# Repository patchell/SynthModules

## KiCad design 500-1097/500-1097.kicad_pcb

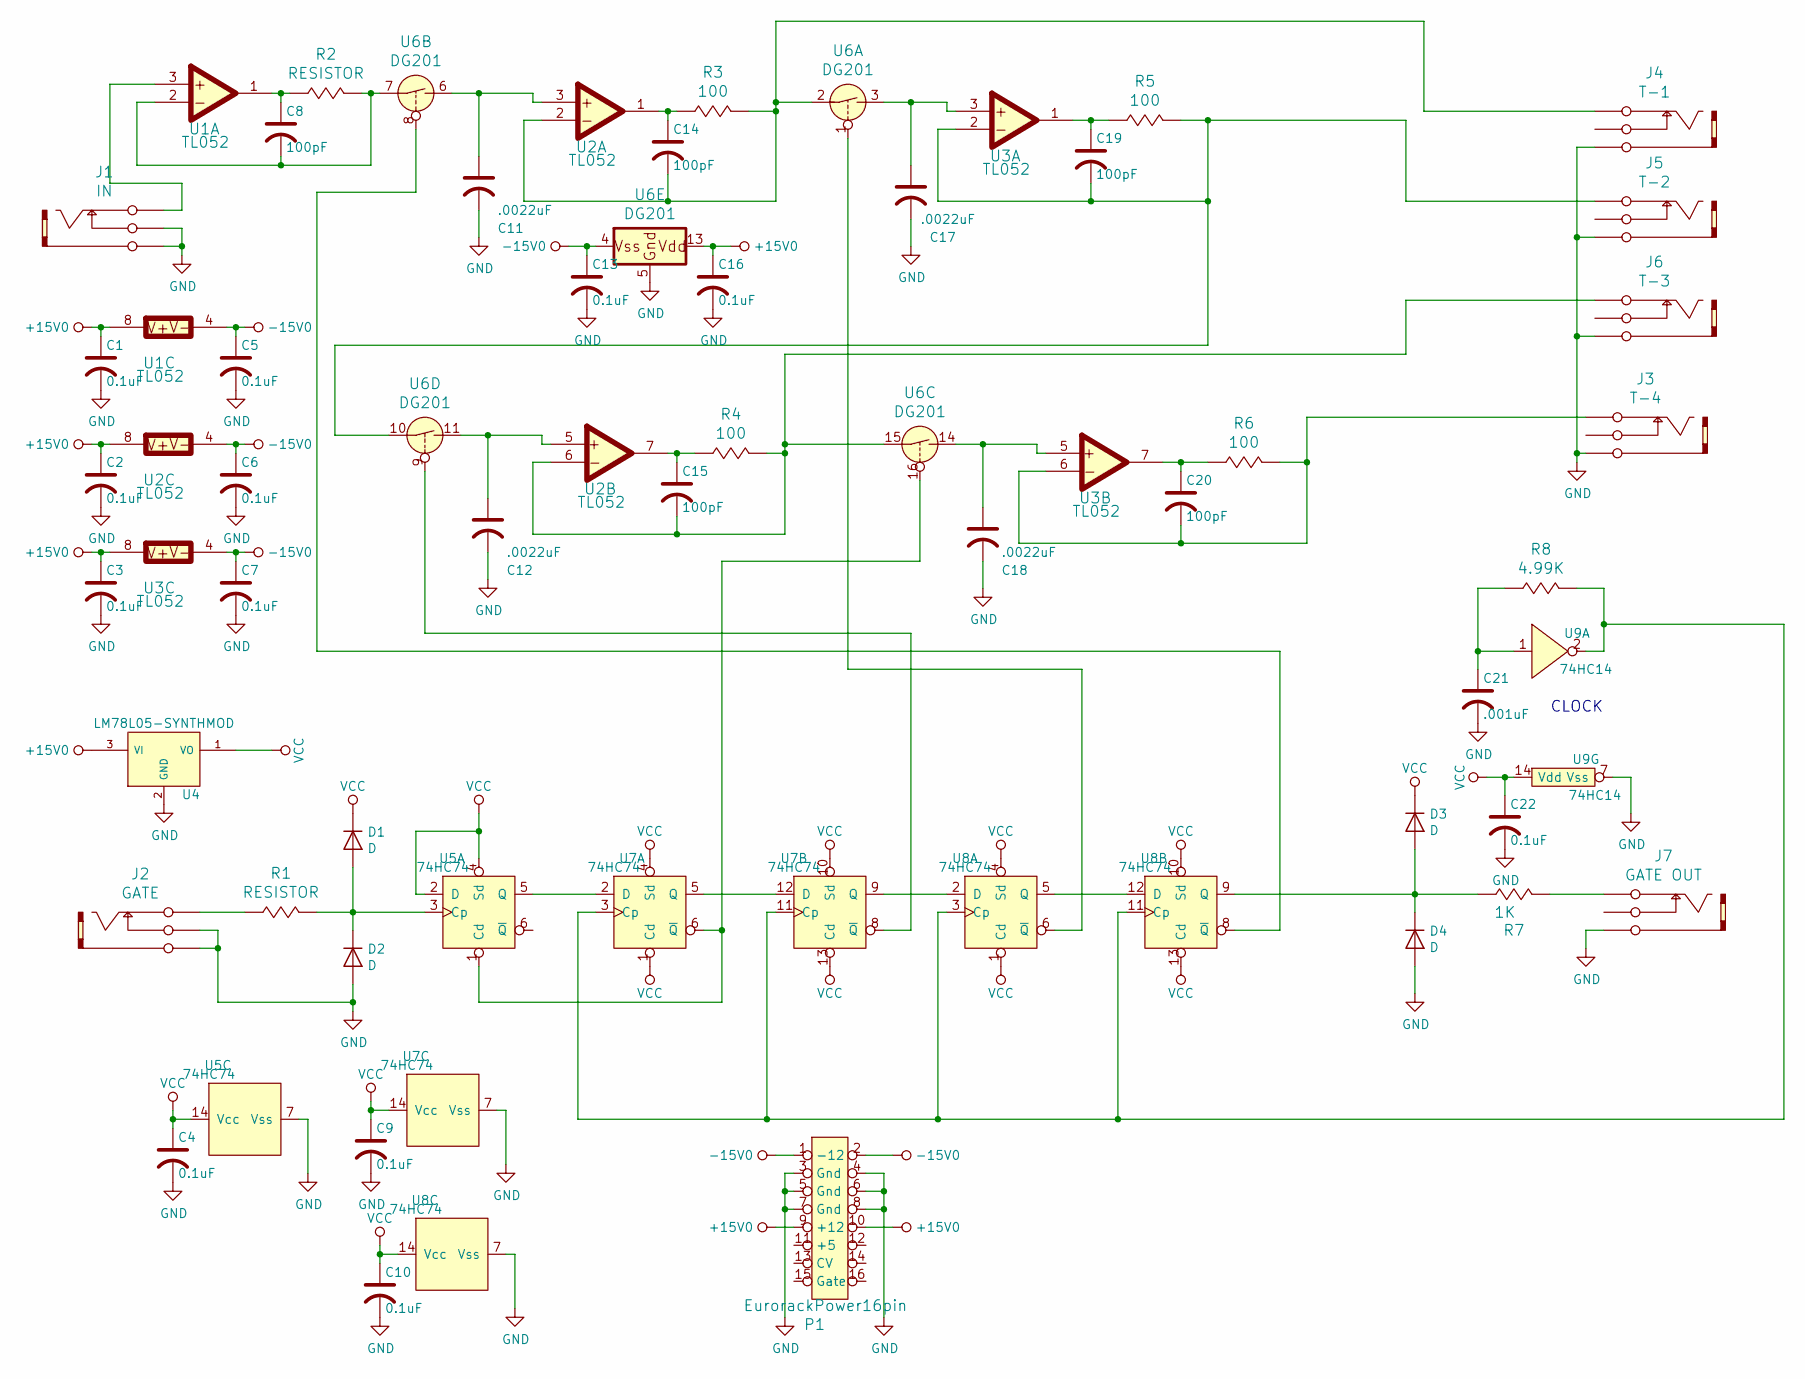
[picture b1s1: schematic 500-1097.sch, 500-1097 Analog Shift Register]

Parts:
C1, C2, C3, C4, C5, C6, C7, C9, C10, C13, C16, C22: 0.1uF; CAP-Bypass-0.3
C8, C14, C15, C19, C20: 100pF; CAP-0.1
C11, C12, C17, C18: .0022uF; CAP-AXIAL-0.5x0.2
C21: .001uF; CAP-GREENIE-0.2
D1, D2, D3, D4: D; DIODE0.4
J1: IN; PHONE-SC112A
J2: GATE; PHONE-SC112A
J3: T-4; PHONE-SC112A
J4: T-1; PHONE-SC112A
J5: T-2; PHONE-SC112A
J6: T-3; PHONE-SC112A
J7: GATE OUT; PHONE-SC112A
P1: EurorackPower16pin; IDC8x2_Vert
R1, R2: RESISTOR; AXIAL0.4
R3, R4, R5, R6: 100; AXIAL0.4
R7: 1K; AXIAL0.4
R8: 4.99K; AXIAL0.4
U1, U2, U3: TL052; DIP8.3
U4: LM78L05-SYNTHMOD; TO92
U5, U7, U8: 74HC74; DIP-14.3
U6: DG201; DIP-16.3
U9: 74HC14; DIP-14.3

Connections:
+15V0: C1.1, C2.1, C3.1, C16.1, P1.9 (+12), P1.10, U1.8 (V+), U2.8 (V+), U3.8 (V+), U4.3 (VI), U6.13 (Vdd)
-15V0: C5.1, C6.1, C7.1, C13.1, P1.1 (-12), P1.2, U1.4 (V-), U2.4 (V-), U3.4 (V-), U6.4 (Vss)
GND: C1.2, C2.2, C3.2, C4.2, C5.2, C6.2, C7.2, C9.2, C10.2, C11.2, C12.2, C13.2, C16.2, C17.2, C18.2, C21.2, C22.2, D2.2 (A), D4.2 (A), J1.1 (Gnd), J1.2 (Sw), J2.1 (Gnd), J2.2 (Sw), J3.1 (Gnd), J4.1 (Gnd), J5.1 (Gnd), J6.1 (Gnd), J7.1 (Gnd), P1.3 (Gnd), P1.4, P1.5 (Gnd), P1.6, P1.7 (Gnd), P1.8, U4.2 (GND), U5.7 (Vss), U6.5 (GND), U7.7 (Vss), U8.7 (Vss), U9.7 (Vss)
unnamed: C8.1, R2.1 (A), U1.1 (OUT)
unnamed: C8.2, R2.2 (B), U1.2 (-), U6.7 (A)
unnamed: C11.1, U2.3 (+), U6.6 (B)
unnamed: C12.1, U2.5 (+), U6.11 (B)
unnamed: C14.1, R3.1 (A), U2.1 (OUT)
unnamed: C14.2, J4.3 (Tip), R3.2 (B), U2.2 (-), U6.2 (A)
unnamed: C15.1, R4.1 (A), U2.7 (OUT)
unnamed: C15.2, J6.3 (Tip), R4.2 (B), U2.6 (-), U6.15 (A)
unnamed: C17.1, U3.3 (+), U6.3 (B)
unnamed: C18.1, U3.5 (+), U6.14 (B)
unnamed: C19.1, R5.1 (A), U3.1 (OUT)
unnamed: C19.2, J5.3 (Tip), R5.2 (B), U3.2 (-), U6.10 (A)
unnamed: C20.1, R6.1 (A), U3.7 (OUT)
unnamed: C20.2, J3.3 (Tip), R6.2 (B), U3.6 (-)
unnamed: C21.1, R8.1 (A), U9.1
unnamed: D1.2 (A), D2.1 (K), R1.2 (B), U5.3 (Cp)
unnamed: D3.2 (A), D4.1 (K), R7.1 (A), U8.9 (Q)
unnamed: J1.3 (Tip), U1.3 (+)
unnamed: J2.3 (Tip), R1.1 (A)
unnamed: J7.3 (Tip), R7.2 (B)
unnamed: R8.2 (B), U7.3 (Cp), U7.11 (Cp), U8.3 (Cp), U8.11 (Cp), U9.2
unnamed: U5.1 (Cd), U6.16 (C), U7.6 (~Q)
unnamed: U5.5 (Q), U7.2 (D)
unnamed: U6.1 (C), U8.6 (~Q)
unnamed: U6.8 (C), U8.8 (~Q)
unnamed: U6.9 (C), U7.8 (~Q)
unnamed: U7.9 (Q), U8.2 (D)
unnamed: U7.5 (Q), U7.12 (D)
unnamed: U8.5 (Q), U8.12 (D)
VCC: C4.1, C9.1, C10.1, C22.1, D1.1 (K), D3.1 (K), U4.1 (VO), U5.2 (D), U5.4 (Sd), U5.14 (Vcc), U7.1 (Cd), U7.4 (Sd), U7.10 (Sd), U7.13 (Cd), U7.14 (Vcc), U8.1 (Cd), U8.4 (Sd), U8.10 (Sd), U8.13 (Cd), U8.14 (Vcc), U9.14 (Vdd)

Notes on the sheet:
CLOCK

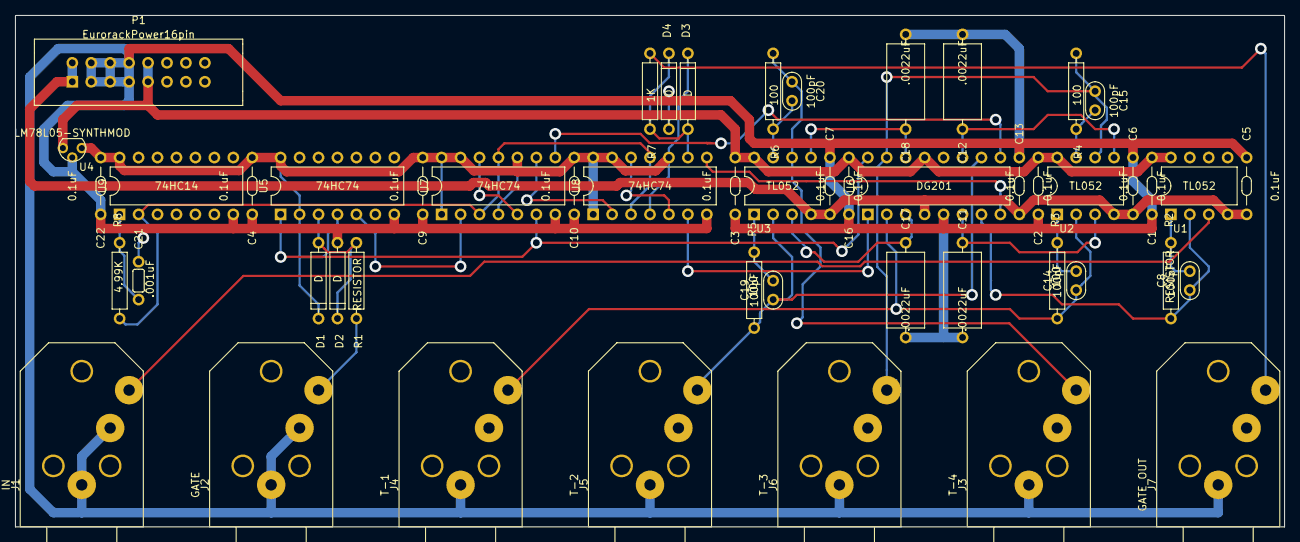
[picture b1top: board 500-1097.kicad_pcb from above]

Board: 2 copper layers, 170.2 x 68.6 mm, 51 parts (0 on the bottom side), 33 nets.

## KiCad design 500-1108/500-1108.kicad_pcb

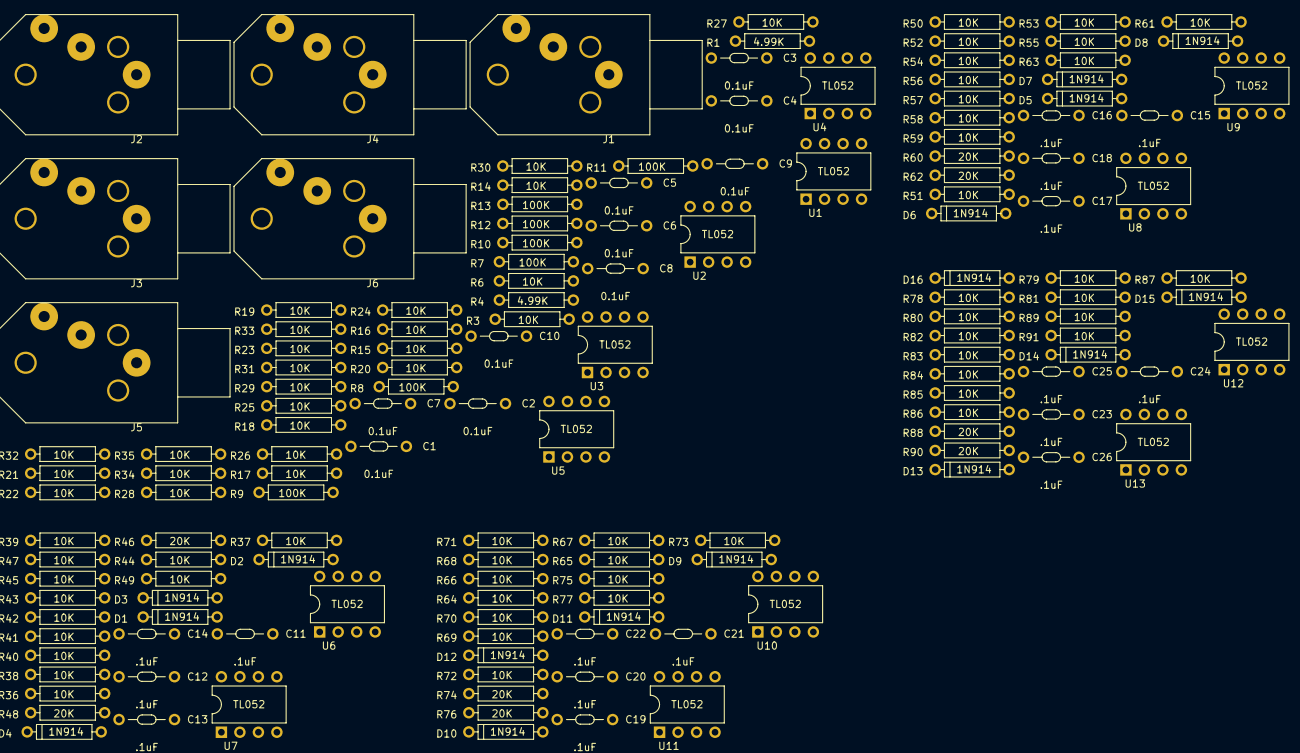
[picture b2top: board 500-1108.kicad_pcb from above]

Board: 2 copper layers, 150 parts (0 on the bottom side), 73 nets, no tracks yet.

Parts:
C1, C2, C3, C4, C5, C6, C7, C8, C9, C10: 0.1uF; CAP-Bypass-0.3
C11, C12, C13, C14, C15, C16, C17, C18, C19, C20, C21, C22, C23, C24, C25, C26: .1uF; CAP-Bypass-0.3
D1, D2, D3, D4, D5, D6, D7, D8, D9, D10, D11, D12, D13, D14, D15, D16: 1N914; DIODE0.4
J1: CV1; PHONE-SC112A
J2: CV2; PHONE-SC112A
J3: Vin; PHONE-SC112A
J4: OUT_2; PHONE-SC112A
J5: OUT_1; PHONE-SC112A
J6: OUT_4; PHONE-SC112A
R1, R4: 4.99K; AXIAL0.4
R3, R6, R14, R15, R16, R17, R18, R19, R20, R21, R22, R23, R24, R25, R26, R27, R28, R29, R30, R31, R32, R33, R34, R35, R36, R37, R38, R39, R40, R41, R42, R43, R44, R45, R47, R49, R50, R51, R52, R53, R54, R55, R56, R57, R58, R59, R61, R63, R64, R65, R66, R67, R68, R69, R70, R71, R72, R73, R75, R77, R78, R79, R80, R81, R82, R83, R84, R85, R86, R87, R89, R91: 10K; AXIAL0.4
R7, R8, R9, R10, R11, R12, R13: 100K; AXIAL0.4
R46, R48, R60, R62, R74, R76, R88, R90: 20K; AXIAL0.4
U1, U2, U3, U4, U5, U6, U7, U8, U9, U10, U11, U12, U13: TL052; DIP8.3

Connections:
+15V0: C1.1, C2.1, C3.1, C7.1, C9.1, C11.1, C13.1, C15.1, C17.1, C19.1, C21.1, C23.1, C25.1, R4.1, U1.8, U2.8, U3.8, U4.8, U5.8, U6.8, U7.8, U8.8, U9.8, U10.8, U11.8, U12.8, U13.8
-15V0: C4.1, C5.1, C6.1, C8.1, C10.1, C12.1, C14.1, C16.1, C18.1, C20.1, C22.1, C24.1, C26.1, R1.1, U1.4, U2.4, U3.4, U4.4, U5.4, U6.4, U7.4, U8.4, U9.4, U10.4, U11.4, U12.4, U13.4
/Wave Multiplier Cell 1/Dfa: D3.2, R14.1, R40.2, R44.1
/Wave Multiplier Cell 1/Dfb: D2.1, R15.1, R43.2, R45.1
/Wave Multiplier Cell 1/Va-: R11.1, R12.2, R37.1, R51.1, R65.1, R79.1, U2.1
/Wave Multiplier Cell 1/Vb+: R13.2, R39.1, R53.1, R67.1, R81.1, U2.7
/Wave Multiplier Cell 1/Vin+: R3.1, R36.1, R46.1, U1.1, U1.2
/Wave Multiplier Cell 1/Vin-: R6.2, R38.1, U1.7
/Wave Multiplier Cell 2/Dfa: D7.2, R17.1, R20.1, R54.2, R58.1
/Wave Multiplier Cell 2/Dfb: D6.1, R18.1, R21.1, R57.2, R59.1
/Wave Multiplier Cell 2/Vin+: R49.2, R50.1, R60.1, U7.7
/Wave Multiplier Cell 2/Vin-: R47.1, R48.2, R52.1, U7.1
/Wave Multiplier Cell 3/Dfa: D11.2, R24.1, R68.2, R72.1
/Wave Multiplier Cell 3/Dfb: D10.1, R25.1, R71.2, R73.1
/Wave Multiplier Cell 3/Vin+: R63.2, R64.1, R74.1, U9.7
/Wave Multiplier Cell 3/Vin-: R61.1, R62.2, R66.1, U9.1
/Wave Multiplier Cell 4/Dfa: D15.2, R28.1, R31.1, R82.2, R86.1
/Wave Multiplier Cell 4/Dfb: D14.1, R29.1, R32.1, R85.2, R87.1
/Wave Multiplier Cell 4/Vin+: R77.2, R78.1, R88.1, U11.7
/Wave Multiplier Cell 4/Vin-: R75.1, R76.2, R80.1, U11.1
/Wave Multiplier Cell 4/Vo+: J5.3, R91.2, U13.7
/Wave Multiplier Cell 4/Vo-: R89.1, R90.2, U13.1
GND: C1.2, C2.2, C3.2, C4.2, C5.2, C6.2, C7.2, C8.2, C9.2, C10.2, C11.2, C12.2, C13.2, C14.2, C15.2, C16.2, C17.2, C18.2, C19.2, C20.2, C21.2, C22.2, C23.2, C24.2, C25.2, C26.2, J1.1, J1.2, J2.1, J2.2, J3.1, J3.2, J4.1, J5.1, J6.1, U1.5, U2.3, U2.5, U3.3, U3.5, U4.3, U4.5, U5.3, U5.5, U6.3, U6.5, U7.3, U7.5, U8.3, U8.5, U9.3, U9.5, U10.3, U10.5, U11.3, U11.5, U12.3, U12.5, U13.3, U13.5
unnamed: D1.1, R41.2
unnamed: D1.2, D3.1, U6.1
unnamed: D2.2, D4.1, U6.7
unnamed: D4.2, R42.2
unnamed: D5.1, R55.2
unnamed: D5.2, D7.1, U8.1
unnamed: D6.2, D8.1, U8.7
unnamed: D8.2, R56.2
unnamed: D9.1, R69.2
unnamed: D10.2, D12.1, U10.7
unnamed: D9.2, D11.1, U10.1
unnamed: D12.2, R70.2
unnamed: D13.1, R83.2
unnamed: D13.2, D15.1, U12.1
unnamed: D14.2, D16.1, U12.7
unnamed: D16.2, R84.2
unnamed: J1.3, R9.1
unnamed: J2.3, R10.1
unnamed: J3.3, U1.3
unnamed: J4.3, R34.2, U5.1
unnamed: J6.3, R35.2, U4.1
unnamed: R3.2, R6.1, U1.6
unnamed: R8.2, R9.2, R10.2, R12.1, U2.2
unnamed: R7.2, R11.2, R13.1, U2.6
unnamed: R14.2, R15.2, R16.1, U3.2
unnamed: R16.2, R19.1, U3.1
unnamed: R17.2, R18.2, R19.2, R22.1, U3.6
unnamed: R20.2, R21.2, R23.1, U4.6
unnamed: R22.2, R26.1, U3.7
unnamed: R23.2, R33.1, U4.7
unnamed: R24.2, R25.2, R26.2, R27.1, U5.6
unnamed: R27.2, R30.1, U5.7
unnamed: R28.2, R29.2, R30.2, R34.1, U5.2
unnamed: R31.2, R32.2, R33.2, R35.1, U4.2
unnamed: R36.2, R37.2, R40.1, R41.1, U6.2
unnamed: R38.2, R39.2, R42.1, R43.1, U6.6
unnamed: R44.2, R45.2, R46.2, R48.1, U7.2
unnamed: R47.2, R49.1, U7.6
unnamed: R50.2, R51.2, R54.1, R55.1, U8.2
unnamed: R52.2, R53.2, R56.1, R57.1, U8.6
unnamed: R58.2, R59.2, R60.2, R62.1, U9.2
unnamed: R61.2, R63.1, U9.6
unnamed: R64.2, R65.2, R68.1, R69.1, U10.2
unnamed: R66.2, R67.2, R70.1, R71.1, U10.6
unnamed: R72.2, R73.2, R74.2, R76.1, U11.2
unnamed: R75.2, R77.1, U11.6
unnamed: R78.2, R79.2, R82.1, R83.1, U12.2
unnamed: R80.2, R81.2, R84.1, R85.1, U12.6
unnamed: R86.2, R87.2, R88.2, R90.1, U13.2
unnamed: R89.2, R91.1, U13.6

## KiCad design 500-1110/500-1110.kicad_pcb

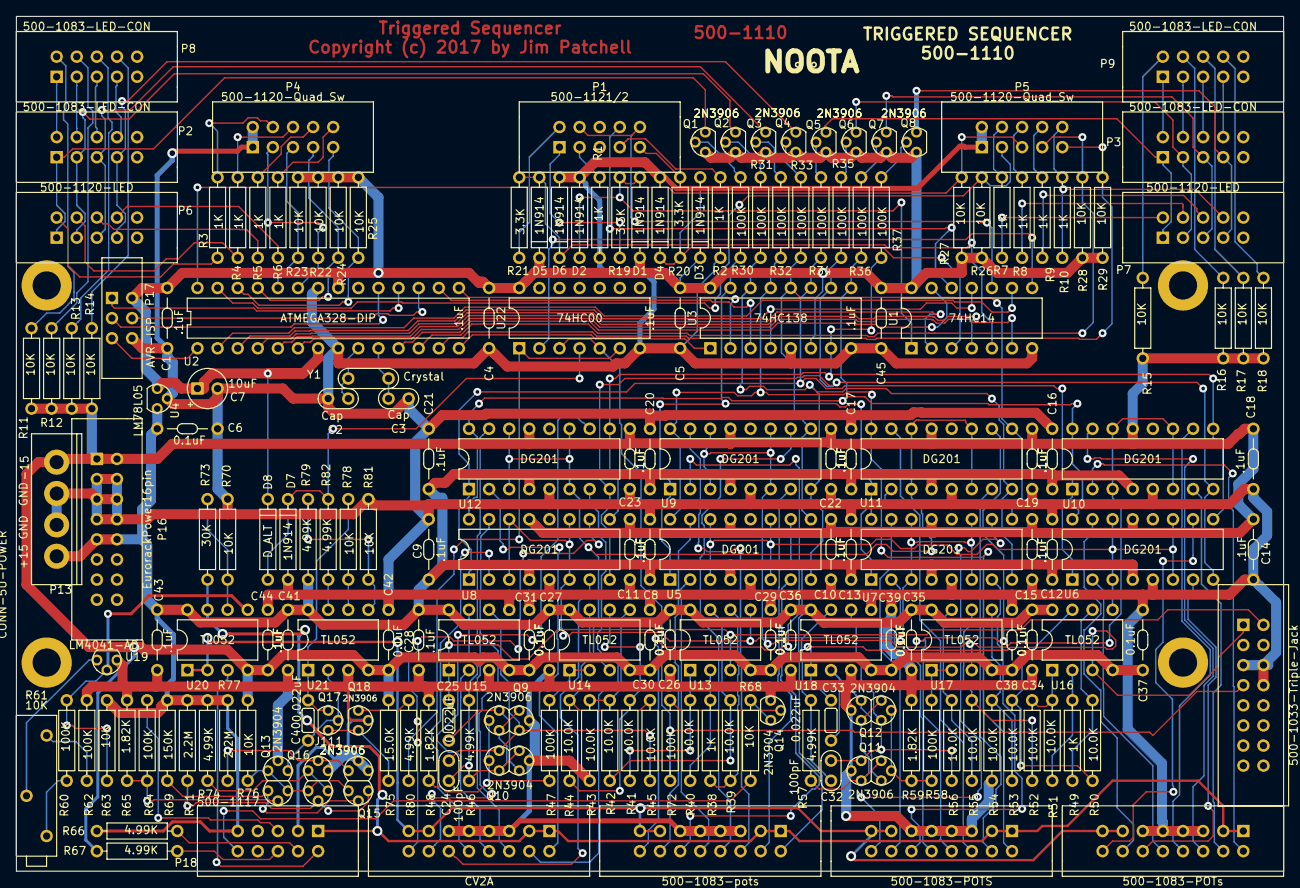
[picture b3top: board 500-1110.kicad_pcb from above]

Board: 2 copper layers, 160.0 x 107.9 mm, 194 parts (0 on the bottom side), 188 nets.

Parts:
C1, C4, C5, C8, C9, C10, C11, C12, C13, C14, C15, C16, C17, C18, C19, C20, C21, C22, C23, C41, C42, C43, C44, C45: .1uF; CAP-Bypass-0.3
C2, C3: Cap; CAP-0.1
C6, C26, C27, C28, C29, C30, C31, C34, C35, C36, C37, C38, C39: 0.1uF; CAP-Bypass-0.3
C7: 10uF; Cap-Pol-Rad-0.2_0.1
C24, C32: 100pF; CAP-0.1
C25, C33, C40: 0.022uF; CAP-GREENIE-0.2
D1, D2, D3, D4, D5, D6, D7: 1N914; DIODE0.4
D8: D_ALT; DIODE0.4
P1: 500-1121/2; IDC5x2_Vert
P2, P3, P8, P9: 500-1083-LED-CON; IDC5x2_Vert
P4, P5: 500-1120-Quad_Sw; IDC5x2_Vert
P6, P7: 500-1120-LED; IDC5x2_Vert
P10: 500-1033-Triple-Jack; IDC8x2_Vert
P11: 500-1083-pots; IDC8x2_Vert
P12: 500-1083-POTs; IDC8x2_Vert
P13: CONN-5U-POWER; MTA0156x4_Vert
P14: 500-1083-POTS; IDC8x2_Vert
P15: CV2A; IDC8x2_Vert
P16: EurorackPower16pin; IDC8x2_Vert
P17: AVR-ISP; IDC3X2
P18: 500-1117; IDC5x2_Vert
Q1, Q2, Q3, Q4, Q5, Q6, Q7, Q8, Q18: 2N3906; TO92
Q9, Q11, Q15, Q16: 2N3906; DUAL_TO92
Q10, Q12, Q13: 2N3904; DUAL_TO92
Q14: 2N3904; TO92
Q17: J111; TO92
R1, R2, R3, R4, R5, R6, R7, R8, R9, R10, R38, R49: 1K; AXIAL0.4
R11, R12, R13, R14, R15, R16, R17, R18, R22, R23, R24, R25, R26, R27, R28, R29, R63, R68, R70, R76, R78, R81: 10K; AXIAL0.4
R19, R20, R21: 3.3K; AXIAL0.4
R30, R31, R32, R33, R34, R35, R36, R37, R47, R58, R60, R62, R64, R72: 100K; AXIAL0.4
R39, R40, R41, R42, R43, R44, R45, R50, R51, R52, R53, R54, R55, R56: 10.0K; AXIAL0.4
R46, R57, R66, R67, R74, R79, R80, R82: 4.99K; AXIAL0.4
R48, R59, R65: 1.82K; AXIAL0.4
R61: 10K; Trimpot-3006
R69: 150K; AXIAL0.4
R71, R77: 2.2M; AXIAL0.4
R73: 30K; AXIAL0.4
R75: 15.0K; AXIAL0.4
U1: 74HC14; DIP-14.3
U2: ATMEGA328-DIP; DIP28.3
U3: 74HC138; DIP-16.3
U4: LM78L05; TO92
U5, U6, U7, U8, U9, U10, U11, U12: DG201; DIP-16.3
U13, U14, U15, U16, U17, U18, U20, U21: TL052; DIP8.3
U19: LM4041-ADJ; TO92
U22: 74HC00; DIP-14.3
Y1: Crystal; XTAL

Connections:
+15V0: C6.1, C8.1, C9.1, C12.1, C13.1, C16.1, C17.1, C20.1, C21.1, C26.1, C27.1, C28.1, C34.1, C35.1, C36.1, C41.1, C43.1, P13.1, P16.9, P16.10, P18.9, R63.1, R66.2, R69.2, R71.2, R74.2, R77.2, R79.2, U4.3, U5.4, U6.4, U7.4, U8.4, U9.4, U10.4, U11.4, U12.4, U13.8, U14.8, U15.8, U16.8, U17.8, U18.8, U20.8, U21.8
-15V0: C10.1, C11.1, C14.1, C15.1, C18.1, C19.1, C22.1, C23.1, C29.1, C30.1, C31.1, C37.1, C38.1, C39.1, C42.1, C44.1, P13.4, P16.1, P16.2, R11.2, R12.2, R13.2, R14.2, R15.2, R16.2, R17.2, R18.2, R67.2, R75.2, R76.2, U5.13, U6.13, U7.13, U8.13, U9.13, U10.13, U11.13, U12.13, U13.4, U14.4, U15.4, U16.4, U17.4, U18.4, U20.4, U21.4
/ARM: P1.8, U1.12
/CLK: P1.1, R19.1
/CV1: U5.3, U5.6, U5.11, U5.14, U6.3, U6.6, U6.11, U6.14, U16.5
/CV1_0: P11.10, U5.2
/CV1_1: P11.12, U5.7
/CV1_2: P11.14, U5.15
/CV1_3: P11.16, U5.10
/CV1_4: P12.10, U6.2
/CV1_5: P12.12, U6.7
/CV1_6: P12.14, U6.15
/CV1_7: P12.16, U6.10
/CV2_0: P14.10, U7.2
/CV2_1: P14.12, U7.7
/CV2_2: P14.14, U7.15
/CV2_3: P14.16, U7.10
/CV2_4: P15.10, U8.2
/CV2_5: P15.12, U8.7
/CV2_6: P15.14, U8.15
/CV2_7: P15.16, U8.10
/DOWNBEAT: P1.2, R21.1
/GLD1: U9.3, U9.6, U9.11, U9.14, U10.3, U10.6, U10.11, U10.14, U17.3
/GLD1_0: P11.2, U9.2
/GLD1_1: P11.4, U9.7
/GLD1_2: P11.6, U9.15
/GLD1_3: P11.8, U9.10
/GLD1_4: P12.2, U10.2
/GLD1_5: P12.4, U10.7
/GLD1_6: P12.6, U10.15
/GLD1_7: P12.8, U10.10
/GLD2_0: P14.2, U11.2
/GLD2_1: P14.4, U11.7
/GLD2_2: P14.6, U11.15
/GLD2_3: P14.8, U11.10
/GLD2_4: P15.2, U12.2
/GLD2_5: P15.4, U12.7
/GLD2_6: P15.6, U12.15
/GLD2_7: P15.8, U12.10
/L0: P2.1, P6.1, Q1.3
/L1: P2.3, P6.3, Q2.3
/L2: P2.5, P6.5, Q3.3
/L3: P2.7, P6.7, Q4.3
/L4: P3.1, P7.1, Q5.3
/L5: P3.3, P7.3, Q6.3
/L6: P3.5, P7.5, Q7.3
/L7: P3.7, P7.7, Q8.3
/LOGIC/GATE: U1.8, U22.2
/LOGIC/nARM: U1.13, U2.11
/LOGIC/nCLK: U1.2, U2.4
/LOGIC/nDB: U1.6, U2.6
/LOGIC/nGATTE: U1.9, U2.2
/LOGIC/nRUN: U1.11, U2.3, U3.4
/LOGIC/nTRIG: U1.4, U2.5
/MUX2/O: U7.3, U7.6, U7.11, U7.14, U8.3, U8.6, U8.11, U8.14, U13.5
/MUX4/O: U11.3, U11.6, U11.11, U11.14, U12.3, U12.6, U12.11, U12.14, U14.3
/OUTPUT_BUFFER_1/OUT: C33.2, P10.1, U16.3, U18.1
/OUTPUT_BUFFER_2/OUT: C25.2, P10.2, U13.3, U15.1
/REFERENCE/+10: P11.1, P11.3, P12.1, P12.3, P14.1, P14.3, P15.1, P15.3, P18.1, R73.2, U20.7
/REFERENCE/G_OUT: P10.7, R72.1, U22.3, U22.5
/REFERENCE/SCALED: P11.13, P11.15, P12.13, P12.15, P14.13, P14.15, P15.13, P15.15, U20.1, U20.2
/RUN: P1.4, P1.10, U1.10
/S0: R30.1, U3.15, U5.1, U7.1, U9.1, U11.1
/S1: R31.1, U3.14, U5.8, U7.8, U9.8, U11.8
/S2: R32.1, U3.13, U5.16, U7.16, U9.16, U11.16
/S3: R33.1, U3.12, U5.9, U7.9, U9.9, U11.9
/S4: R34.1, U3.11, U6.1, U8.1, U10.1, U12.1
/S5: R35.1, U3.10, U6.8, U8.8, U10.8, U12.8
/S6: R36.1, U3.9, U6.16, U8.16, U10.16, U12.16
/S7: R37.1, U3.7, U6.9, U8.9, U10.9, U12.9
/TRIG: P1.9, R20.1
/X0: P4.3, R22.1, U2.23
/X1: P4.5, R23.1, U2.24
/X2: P4.7, R24.1, U2.25
/X3: P4.9, R25.1, U2.26
/X4: P5.3, R26.1, U2.27
/X5: P5.5, R27.1, U2.28
/X6: P5.7, R28.1, U2.12
/X7: P5.9, R29.1, U2.13
GND: C1.2, C2.2, C3.2, C4.2, C5.2, C6.2, C7.2, C8.2, C9.2, C10.2, C11.2, C12.2, C13.2, C14.2, C15.2, C16.2, C17.2, C18.2, C19.2, C20.2, C21.2, C22.2, C23.2, C26.2, C27.2, C28.2, C29.2, C30.2, C31.2, C34.2, C35.2, C36.2, C37.2, C38.2, C39.2, C41.2, C42.2, C43.2, C44.2, C45.2, D2.2, D4.2, D6.2, D7.2, P4.1, P4.2, P5.1, P5.2, P10.5, P10.6, P10.8, P11.5, P11.7, P11.9, P11.11, P12.5, P12.7, P12.9, P12.11, P13.2, P13.3, P14.5, P14.7, P14.9, P14.11, P15.5, P15.7, P15.9, P15.11, P16.3, P16.4, P16.5, P16.6, P16.7, P16.8, P17.6, P18.3, Q9.2, Q10.5, Q11.2, Q12.5, Q13.5, Q14.1, Q15.5, Q15.6, Q16.6, Q18.2, R1.2, R2.2, R43.1, R48.2, R54.1, R59.2, R62.2, R65.1, R70.2, R81.2, U1.7, U2.8, U2.22, U3.5, U3.8, U4.2, U5.5, U6.5, U7.5, U8.5, U9.5, U10.5, U11.5, U12.5, U15.3, U15.5, U18.3, U18.5, U19.1, U21.3, U22.7
unnamed: C2.1, U2.9, Y1.1
unnamed: C3.1, U2.10, Y1.2
unnamed: C24.1, Q9.3, Q10.3, R45.1, U15.6
unnamed: C24.2, R46.2, U15.7
unnamed: C25.1, Q9.6, Q10.6, U15.2
unnamed: C32.1, Q11.3, Q12.3, R56.1, U18.6
unnamed: C32.2, R57.2, U18.7
unnamed: C33.1, Q11.6, Q12.6, U18.2
unnamed: C40.1, Q13.6, Q17.2, U21.2
unnamed: C40.2, Q17.1, R78.2, U21.1
unnamed: D1.2, D2.1, R19.2, U1.1
unnamed: D3.2, D4.1, R20.2, U1.3
unnamed: D5.2, D6.1, R21.2, U1.5
unnamed: D7.1, D8.2, R82.1, U22.4
unnamed: P1.3, R1.1
unnamed: P1.7, R2.1
unnamed: P2.2, P8.1
unnamed: P2.4, P8.3
unnamed: P2.6, P8.5
unnamed: P2.8, P8.7
unnamed: P3.2, P9.1
unnamed: P3.4, P9.3
unnamed: P3.6, P9.5
unnamed: P3.8, P9.7
unnamed: P4.4, R3.2
unnamed: P4.6, R4.2
unnamed: P4.8, R5.2
unnamed: P4.10, R6.2
unnamed: P5.4, R7.2
unnamed: P5.6, R8.2
unnamed: P5.8, R9.2
unnamed: P5.10, R10.2
unnamed: P6.2, R3.1
unnamed: P6.4, R4.1
unnamed: P6.6, R5.1
unnamed: P6.8, R6.1
unnamed: P7.2, R7.1
unnamed: P7.4, R8.1
unnamed: P7.6, R9.1
unnamed: P7.8, R10.1
unnamed: P8.2, R11.1
unnamed: P8.4, R12.1
unnamed: P8.6, R13.1
unnamed: P8.8, R14.1
unnamed: P9.2, R15.1
unnamed: P9.4, R16.1
unnamed: P9.6, R17.1
unnamed: P9.8, R18.1
unnamed: P17.1, U2.18
unnamed: P17.3, U2.19
unnamed: P17.4, U2.17
unnamed: P17.5, U2.1
unnamed: P18.2, U20.3
unnamed: P18.4, R66.1
unnamed: P18.5, R64.2
unnamed: P18.6, R67.1
unnamed: P18.10, R68.2
unnamed: Q1.2, R30.2
unnamed: Q2.2, R31.2
unnamed: Q3.2, R32.2
unnamed: Q4.2, R33.2
unnamed: Q5.2, R34.2
unnamed: Q6.2, R35.2
unnamed: Q7.2, R36.2
unnamed: Q8.2, R37.2
unnamed: Q9.1, Q9.4, Q10.1, Q10.4, R46.1
unnamed: Q9.5, Q10.2, R47.1, R48.1
unnamed: Q11.1, Q11.4, Q12.1, Q12.4, R57.1
unnamed: Q11.5, Q12.2, R58.1, R59.1
unnamed: Q13.1, Q13.4, Q15.3, Q16.3, R76.1
unnamed: Q13.2, R64.1, R65.2
unnamed: Q13.3, Q15.2, R69.1
unnamed: Q14.2, R72.2
unnamed: Q14.3, R68.1
unnamed: Q15.1, Q16.2, R71.1
unnamed: Q15.4, Q16.5, R77.1
unnamed: Q16.1, Q16.4, R74.1
unnamed: Q17.3, Q18.3, R75.1
unnamed: Q18.1, R80.2
unnamed: R38.1, R39.2, U13.6
unnamed: R38.2, R40.2, U13.2
unnamed: R39.1, R42.2, U13.7
unnamed: R40.1, R41.2, U13.1
unnamed: R41.1, R44.2, U14.6
unnamed: R42.1, R43.2, U14.5
unnamed: R44.1, R45.2, U14.7
unnamed: R47.2, U14.1, U14.2
unnamed: R49.1, R50.2, U16.6
unnamed: R49.2, R51.2, U16.2
unnamed: R50.1, R53.2, U16.7
unnamed: R51.1, R52.2, U16.1
unnamed: R52.1, R55.2, U17.6
unnamed: R53.1, R54.2, U17.5
unnamed: R55.1, R56.2, U17.7
unnamed: R58.2, U17.1, U17.2
unnamed: R60.1, R63.2, U19.2, U20.5
unnamed: R60.2, R61.1
unnamed: R61.2, U19.3
unnamed: R61.3, R62.1
unnamed: R70.1, R73.1, U20.6
unnamed: R78.1, U21.6
unnamed: R79.1, R81.1, U21.5
unnamed: R80.1, U22.1, U22.6
unnamed: R82.2, U21.7
unnamed: U2.14, U3.1
unnamed: U2.15, U3.2
unnamed: U2.16, U3.3
VCC: C1.1, C4.1, C5.1, C7.1, C45.1, D1.1, D3.1, D5.1, D8.1, P17.2, Q1.1, Q2.1, Q3.1, Q4.1, Q5.1, Q6.1, Q7.1, Q8.1, R22.2, R23.2, R24.2, R25.2, R26.2, R27.2, R28.2, R29.2, U1.14, U2.7, U2.21, U3.6, U3.16, U4.1, U22.14

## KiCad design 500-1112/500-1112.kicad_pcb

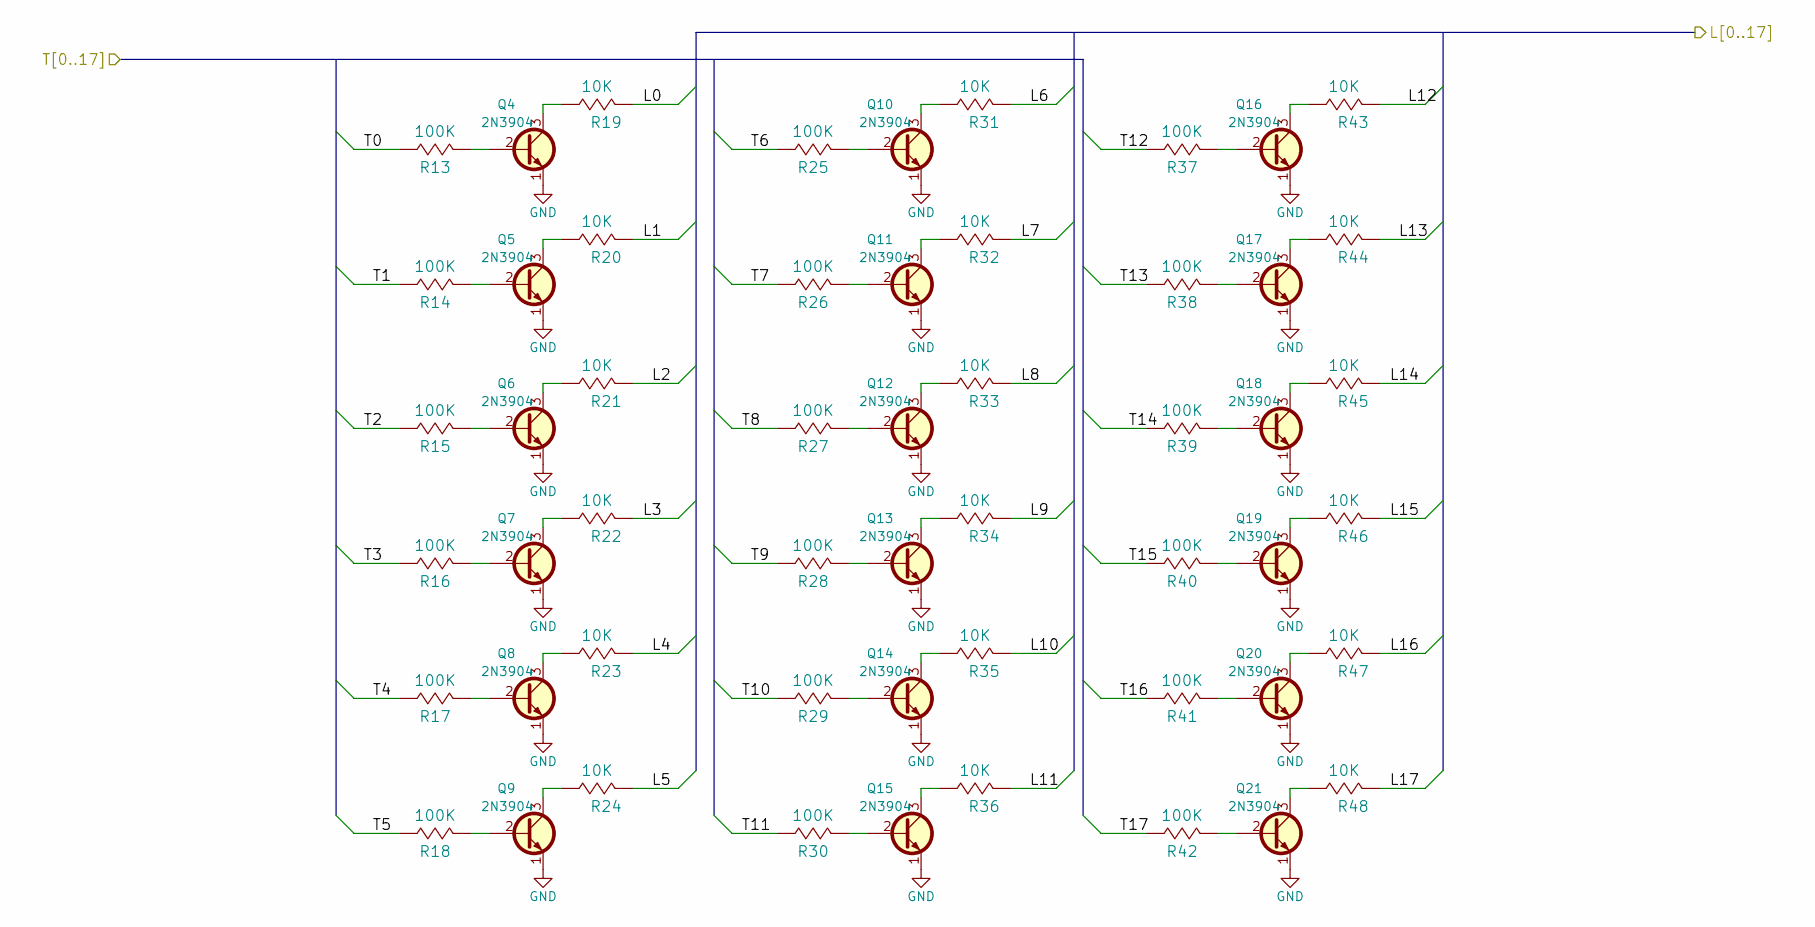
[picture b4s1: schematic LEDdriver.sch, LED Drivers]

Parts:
Q4, Q5, Q6, Q7, Q8, Q9, Q10, Q11, Q12, Q13, Q14, Q15, Q16, Q17, Q18, Q19, Q20, Q21: 2N3904; TO92
R13, R14, R15, R16, R17, R18, R25, R26, R27, R28, R29, R30, R37, R38, R39, R40, R41, R42: 100K; AXIAL0.4
R19, R20, R21, R22, R23, R24, R31, R32, R33, R34, R35, R36, R43, R44, R45, R46, R47, R48: 10K; AXIAL0.4

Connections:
/T0: R13.1 (A); also elsewhere on the board
/T1: R14.1 (A); also elsewhere on the board
/T2: R15.1 (A); also elsewhere on the board
/T3: R16.1 (A); also elsewhere on the board
/T4: R17.1 (A); also elsewhere on the board
/T5: R18.1 (A); also elsewhere on the board
/T6: R25.1 (A); also elsewhere on the board
/T7: R26.1 (A); also elsewhere on the board
/T8: R27.1 (A); also elsewhere on the board
/T9: R28.1 (A); also elsewhere on the board
/T10: R29.1 (A); also elsewhere on the board
/T11: R30.1 (A); also elsewhere on the board
/T12: R37.1 (A); also elsewhere on the board
/T13: R38.1 (A); also elsewhere on the board
/T14: R39.1 (A); also elsewhere on the board
/T15: R40.1 (A); also elsewhere on the board
/T16: R41.1 (A); also elsewhere on the board
/T17: R42.1 (A); also elsewhere on the board
/TLD0: R19.2 (B); also elsewhere on the board
/TLD1: R20.2 (B); also elsewhere on the board
/TLD2: R21.2 (B); also elsewhere on the board
/TLD3: R22.2 (B); also elsewhere on the board
/TLD4: R23.2 (B); also elsewhere on the board
/TLD5: R24.2 (B); also elsewhere on the board
/TLD6: R31.2 (B); also elsewhere on the board
/TLD7: R32.2 (B); also elsewhere on the board
/TLD8: R33.2 (B); also elsewhere on the board
/TLD9: R34.2 (B); also elsewhere on the board
/TLD10: R35.2 (B); also elsewhere on the board
/TLD11: R36.2 (B); also elsewhere on the board
/TLD12: R43.2 (B); also elsewhere on the board
/TLD13: R44.2 (B); also elsewhere on the board
/TLD14: R45.2 (B); also elsewhere on the board
/TLD15: R46.2 (B); also elsewhere on the board
/TLD16: R47.2 (B); also elsewhere on the board
/TLD17: R48.2 (B); also elsewhere on the board
GND: Q4.1 (E), Q5.1 (E), Q6.1 (E), Q7.1 (E), Q8.1 (E), Q9.1 (E), Q10.1 (E), Q11.1 (E), Q12.1 (E), Q13.1 (E), Q14.1 (E), Q15.1 (E), Q16.1 (E), Q17.1 (E), Q18.1 (E), Q19.1 (E), Q20.1 (E), Q21.1 (E); also elsewhere on the board
unnamed: Q4.2 (B), R13.2 (B)
unnamed: Q4.3 (C), R19.1 (A)
unnamed: Q5.2 (B), R14.2 (B)
unnamed: Q5.3 (C), R20.1 (A)
unnamed: Q6.2 (B), R15.2 (B)
unnamed: Q6.3 (C), R21.1 (A)
unnamed: Q7.2 (B), R16.2 (B)
unnamed: Q7.3 (C), R22.1 (A)
unnamed: Q8.2 (B), R17.2 (B)
unnamed: Q8.3 (C), R23.1 (A)
unnamed: Q9.2 (B), R18.2 (B)
unnamed: Q9.3 (C), R24.1 (A)
unnamed: Q10.2 (B), R25.2 (B)
unnamed: Q10.3 (C), R31.1 (A)
unnamed: Q11.2 (B), R26.2 (B)
unnamed: Q11.3 (C), R32.1 (A)
unnamed: Q12.2 (B), R27.2 (B)
unnamed: Q12.3 (C), R33.1 (A)
unnamed: Q13.2 (B), R28.2 (B)
unnamed: Q13.3 (C), R34.1 (A)
unnamed: Q14.2 (B), R29.2 (B)
unnamed: Q14.3 (C), R35.1 (A)
unnamed: Q15.2 (B), R30.2 (B)
unnamed: Q15.3 (C), R36.1 (A)
unnamed: Q16.2 (B), R37.2 (B)
unnamed: Q16.3 (C), R43.1 (A)
unnamed: Q17.2 (B), R38.2 (B)
unnamed: Q17.3 (C), R44.1 (A)
unnamed: Q18.2 (B), R39.2 (B)
unnamed: Q18.3 (C), R45.1 (A)
unnamed: Q19.2 (B), R40.2 (B)
unnamed: Q19.3 (C), R46.1 (A)
unnamed: Q20.2 (B), R41.2 (B)
unnamed: Q20.3 (C), R47.1 (A)
unnamed: Q21.2 (B), R42.2 (B)
unnamed: Q21.3 (C), R48.1 (A)

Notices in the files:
500-1110/500-1110.kicad_pcb:
Copyright (c) 2017 by Jim Patchell
